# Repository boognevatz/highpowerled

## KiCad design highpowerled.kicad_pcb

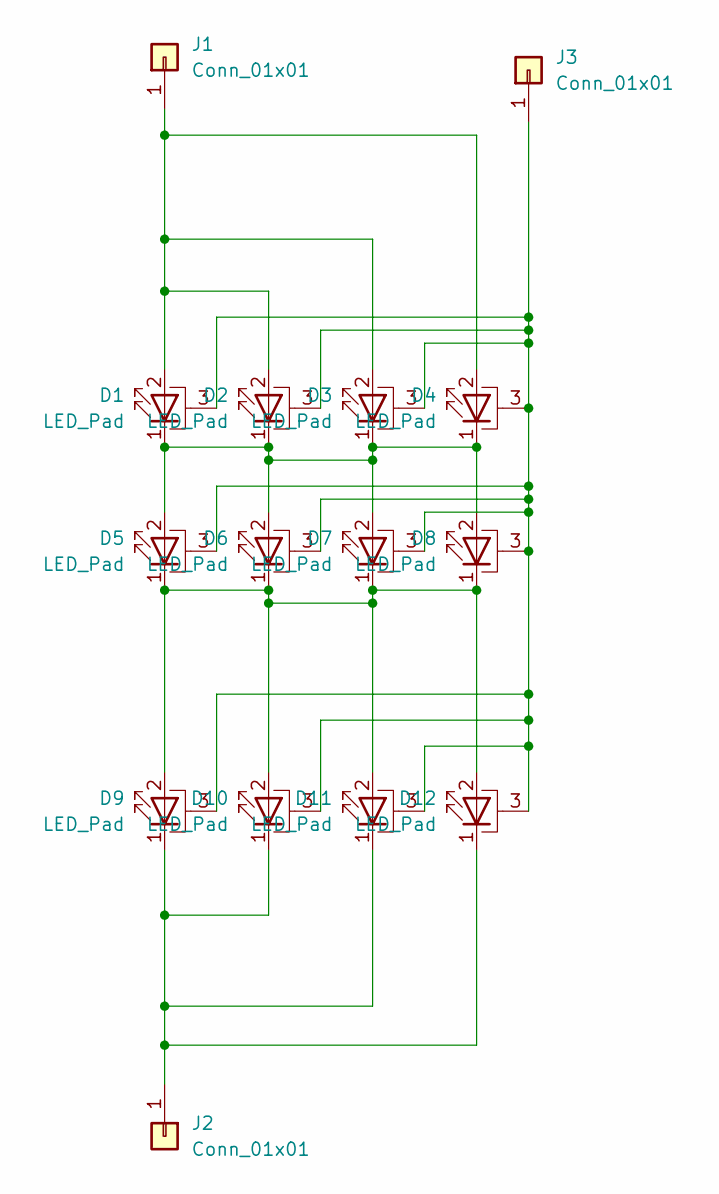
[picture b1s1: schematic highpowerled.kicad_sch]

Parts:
D1, D2, D3, D4, D5, D6, D7, D8, D9, D10, D11, D12: LED_Pad; LM6868
J1, J2, J3: Conn_01x01; CONN_BIG_01X01

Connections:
unnamed: D1.2 (A), D2.2 (A), D3.2 (A), D4.2 (A), J1.1
unnamed: D1.1 (K), D2.1 (K), D3.1 (K), D4.1 (K), D5.2 (A), D6.2 (A), D7.2 (A), D8.2 (A)
unnamed: D1.3 (PAD), D2.3 (PAD), D3.3 (PAD), D4.3 (PAD), D5.3 (PAD), D6.3 (PAD), D7.3 (PAD), D8.3 (PAD), D9.3 (PAD), D10.3 (PAD), D11.3 (PAD), D12.3 (PAD), J3.1
unnamed: D5.1 (K), D6.1 (K), D7.1 (K), D8.1 (K), D9.2 (A), D10.2 (A), D11.2 (A), D12.2 (A)
unnamed: D9.1 (K), D10.1 (K), D11.1 (K), D12.1 (K), J2.1

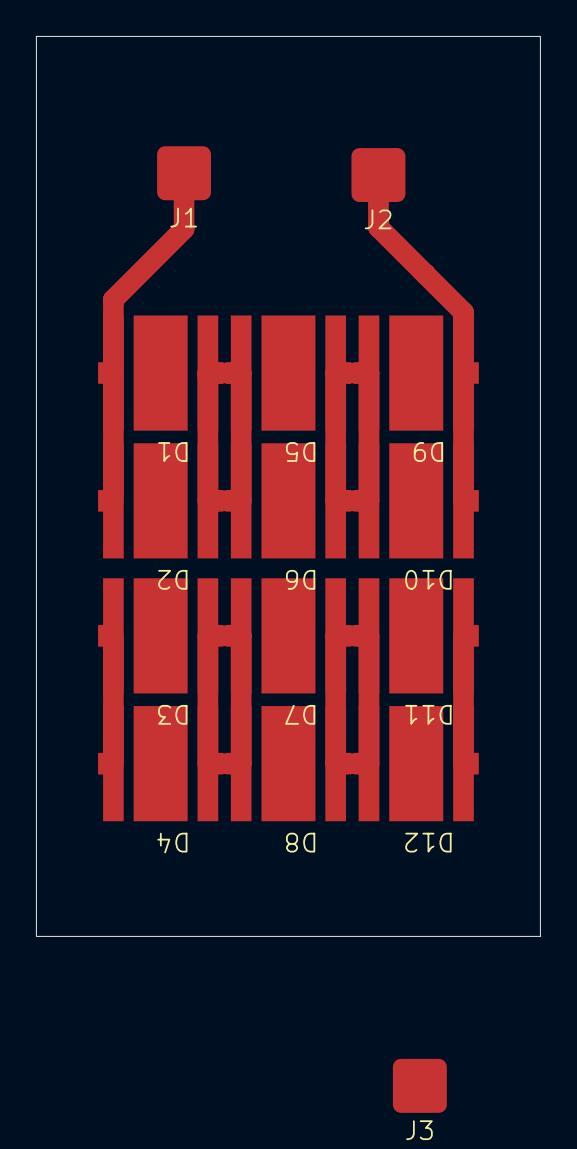
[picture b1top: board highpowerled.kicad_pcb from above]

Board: 2 copper layers, 28.0 x 50.0 mm, 15 parts (0 on the bottom side), 5 nets.

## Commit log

2025-03-15 first version
    The power led added to project library.
